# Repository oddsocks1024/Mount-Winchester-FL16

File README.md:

# Mount Winchester FL16

## Description
A full length 16bit ISA card for mounting hard disks (aka a HardCard). Please note, it's not a hard drive controller but a convenient method of mounting hard drives in legacy systems

**Features**
* Mount up to 3 x 2.5" hard disks
* Mount up to 2 x 3.5" hard disks
* Optionally power the hard Disks directly from the card, by attaching Molex or SATA power cables to any of the 5 x power points
* Useful in PCs and can also be used in the ISA slots of Big Box Amigas as it only needs the ISA slots for power
* Power LED

## Bill of Materials

| Qty | Component                        |
|:---:|----------------------------------|
| 1   | 330Ω Axial Resistor - ¼ watt     |
| 1   | 3mm LED                          |

Molex or SATA power cable "pigtails" (optional up to 5) if you wish to power hard drives directly from the card

## Power
If powering HDs from the card, do not exceed:

* +12V : 1A Total
* +5V (16bit Slot) : 4A Total
* +5V (8bit Slot) : 2.5A Total

Consult the label on your hard drives.

## Support Me
* [My Projects](https://projects.amiga-hardware.com) - Donate on this page
* [Order the Mount Winchester FL16 PCB](https://www.pcbway.com/project/shareproject/Mount_Winchester_FL16_16bit_ISA_HardCard_9fa64691.html)

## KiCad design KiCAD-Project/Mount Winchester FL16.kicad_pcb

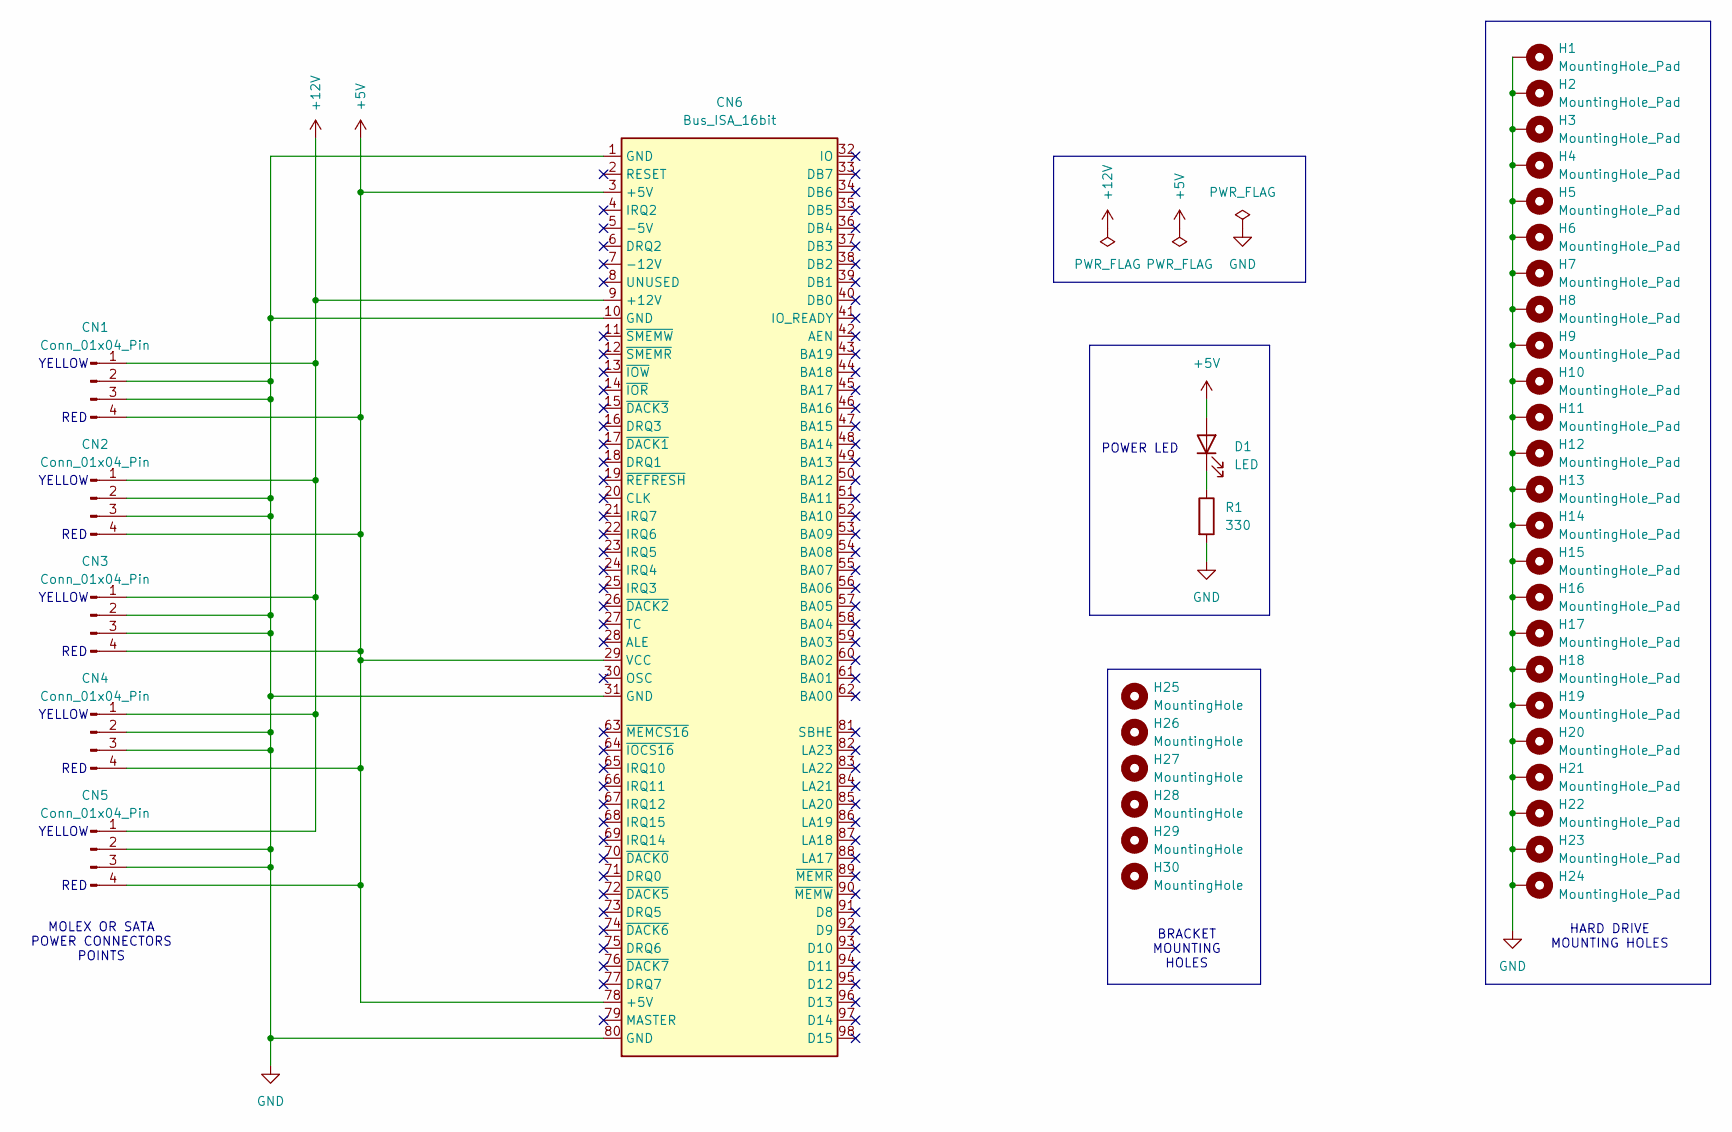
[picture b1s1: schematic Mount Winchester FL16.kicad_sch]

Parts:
CN1, CN2, CN3, CN4, CN5: Conn_01x04_Pin; SolderWire-0.75sqmm_1x04_P4.8mm_D1.25mm_OD2.3mm
CN6: Bus_ISA_16bit; BUS_AT
D1: LED; LED_D3.0mm
H1, H2, H3, H4, H5, H6, H7, H8, H9, H10, H11, H12: MountingHole_Pad; MountingHole_3.5mm_Pad_TopOnly
H13, H14, H15, H16, H17, H18, H19, H20, H21, H22, H23, H24: MountingHole_Pad; MountingHole_3.2mm_M3_DIN965_Pad_TopOnly
H25, H26, H27, H28, H29, H30: MountingHole; MountingHole_3.2mm_M3
R1: 330; R_Axial_DIN0207_L6.3mm_D2.5mm_P10.16mm_Horizontal

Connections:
+5V: CN1.4, CN2.4, CN3.4, CN4.4, CN5.4, CN6.3 (+5V), CN6.29 (VCC), CN6.78 (+5V), D1.2 (A)
+12V: CN1.1, CN2.1, CN3.1, CN4.1, CN5.1, CN6.9 (+12V)
GND: CN1.2, CN1.3, CN2.2, CN2.3, CN3.2, CN3.3, CN4.2, CN4.3, CN5.2, CN5.3, CN6.1 (GND), CN6.10 (GND), CN6.31 (GND), CN6.80 (GND), H1.1, H2.1, H3.1, H4.1, H5.1, H6.1, H7.1, H8.1, H9.1, H10.1, H11.1, H12.1, H13.1, H14.1, H15.1, H16.1, H17.1, H18.1, H19.1, H20.1, H21.1, H22.1, H23.1, H24.1, R1.2
unnamed: D1.1 (K), R1.1

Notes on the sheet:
MOLEX OR SATA POWER CONNECTORS POINTS
RED
YELLOW
BRACKET MOUNTING HOLES
POWER LED
HARD DRIVE MOUNTING HOLES

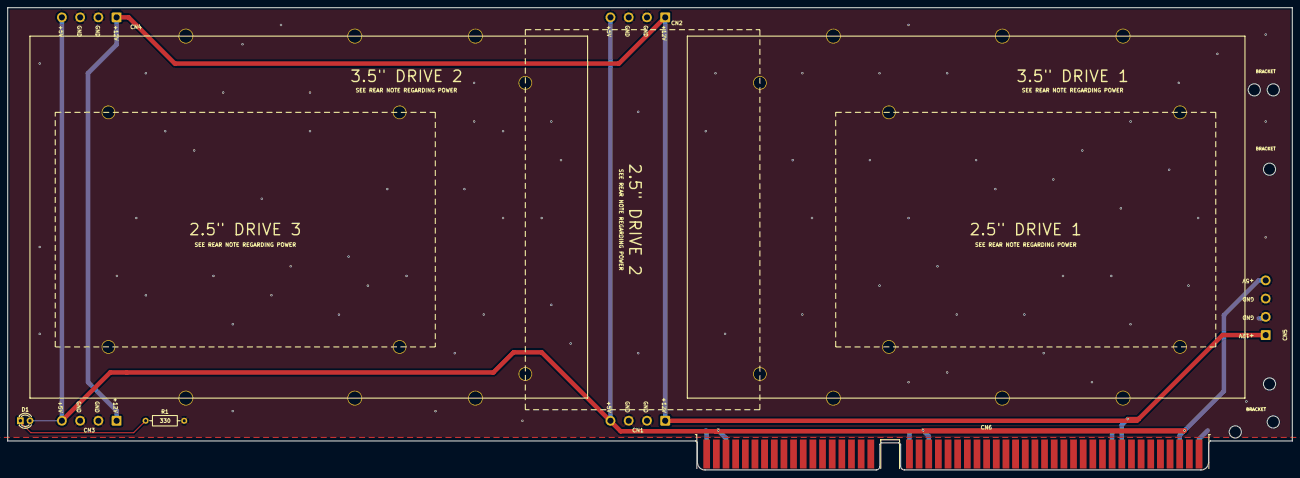
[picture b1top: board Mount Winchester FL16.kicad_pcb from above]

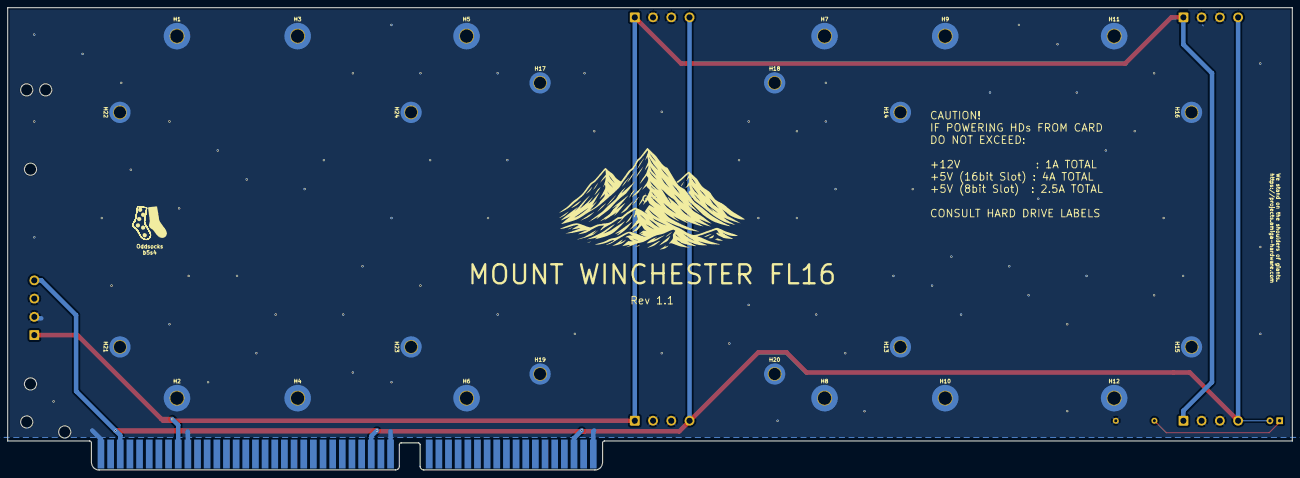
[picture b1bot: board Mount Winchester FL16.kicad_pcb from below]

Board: 2 copper layers, 338.0 x 121.6 mm, 38 parts (24 on the bottom side), 4 nets.

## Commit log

2025-11-29 Add PDF schematics
2025-11-30 Add license file
